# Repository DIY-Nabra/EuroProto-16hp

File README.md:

EURORACK PROTOBOARD 16HP
========================

A universal Eurorack module building system inspired by [Serge Modular Paperface](https://serge-modular.com/paperface),
and Delptronics [Module Construction Set](https://delptronics.com/module-construction-set.php).

All projects in the [DIY-Nabra](https://github.com/DIY-Nabra) repositories are built using this board, or it's little
sibling the [10hp Eurorack Protoboard](https://github.com/DIY-Nabra/EuroProto-10hp)

Licensed under a CC BY-NC-SA 4.0 (Creative Commons Attribution-NonCommercial-ShareAlike 4.0) license.  See the [License File](./LICENSE.md) for more details.

*Front panel*

*Panel components board*

*Front of mainboard*

*Back of mainboard*

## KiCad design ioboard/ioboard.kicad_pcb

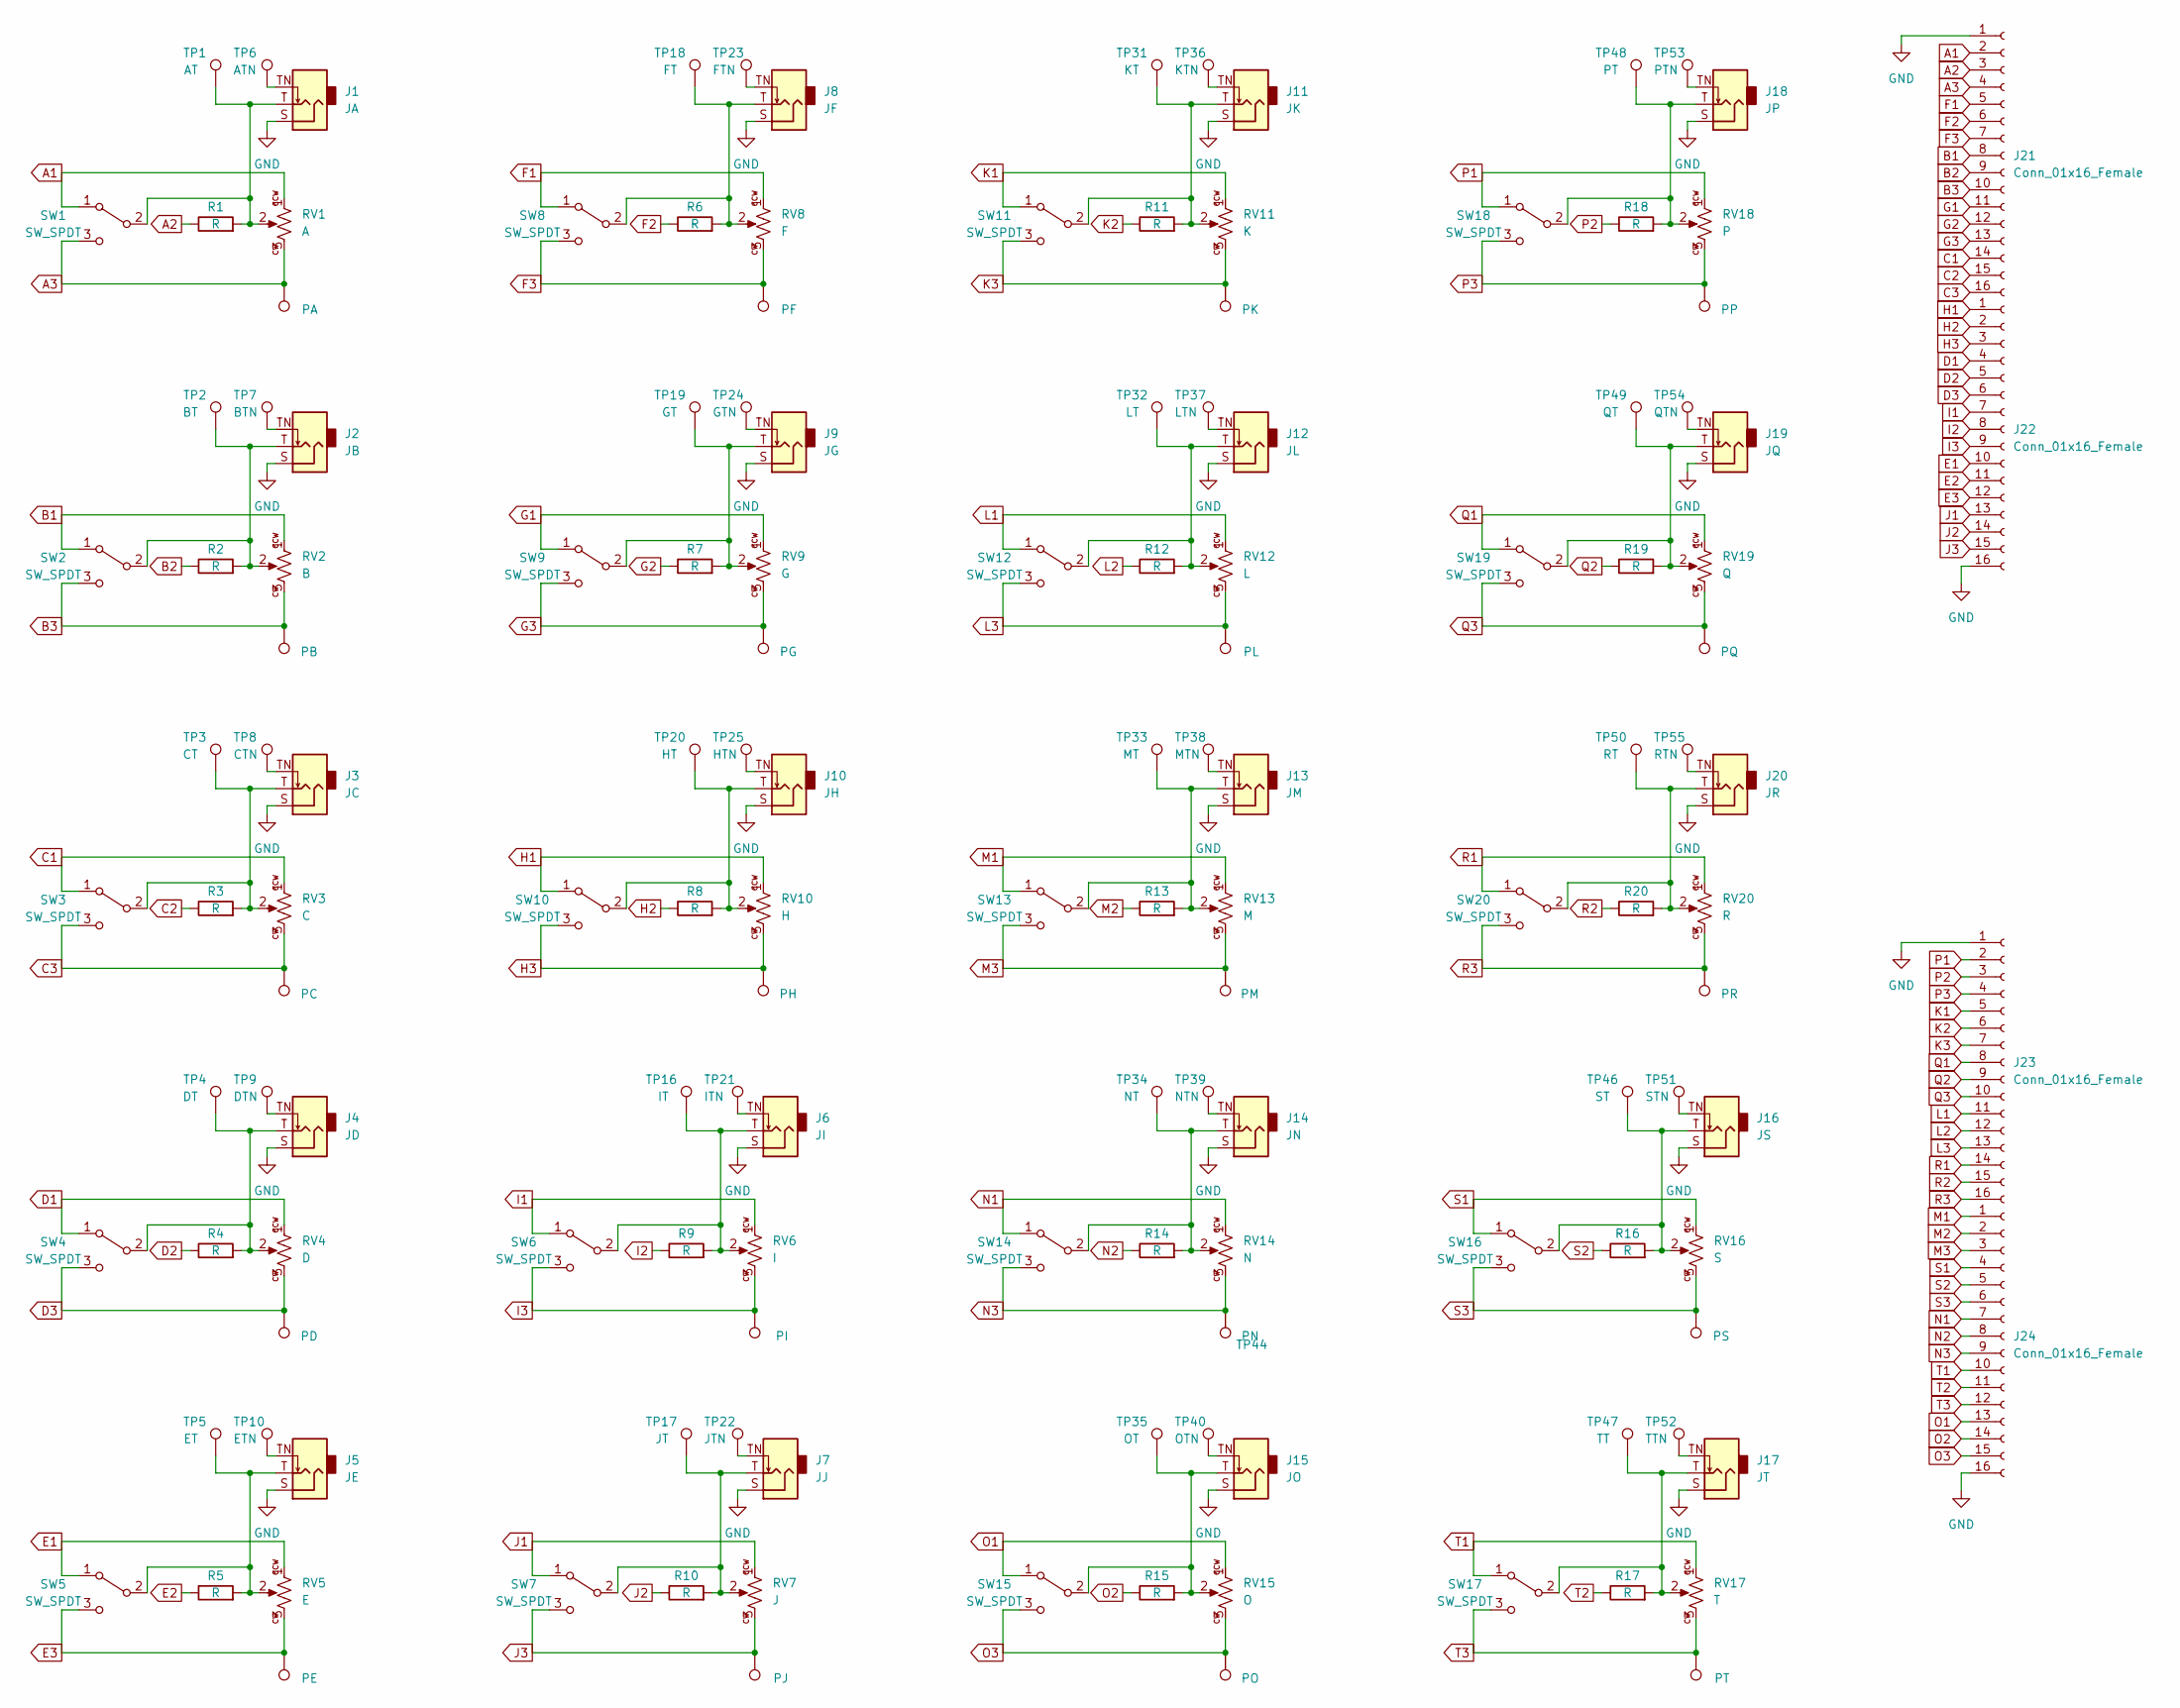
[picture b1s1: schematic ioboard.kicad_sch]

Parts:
J1: JA; slimjackfootprint; MPN WQP-WQP518MA
J2: JB; slimjackfootprint; MPN WQP-WQP518MA
J3: JC; slimjackfootprint; MPN WQP-WQP518MA
J4: JD; slimjackfootprint; MPN WQP-WQP518MA
J5: JE; slimjackfootprint; MPN WQP-WQP518MA
J6: JI; slimjackfootprint; MPN WQP-WQP518MA
J7: JJ; slimjackfootprint; MPN WQP-WQP518MA
J8: JF; slimjackfootprint; MPN WQP-WQP518MA
J9: JG; slimjackfootprint; MPN WQP-WQP518MA
J10: JH; slimjackfootprint; MPN WQP-WQP518MA
J11: JK; slimjackfootprint; MPN WQP-WQP518MA
J12: JL; slimjackfootprint; MPN WQP-WQP518MA
J13: JM; slimjackfootprint; MPN WQP-WQP518MA
J14: JN; slimjackfootprint; MPN WQP-WQP518MA
J15: JO; slimjackfootprint; MPN WQP-WQP518MA
J16: JS; slimjackfootprint; MPN WQP-WQP518MA
J17: JT; slimjackfootprint; MPN WQP-WQP518MA
J18: JP; slimjackfootprint; MPN WQP-WQP518MA
J19: JQ; slimjackfootprint; MPN WQP-WQP518MA
J20: JR; slimjackfootprint; MPN WQP-WQP518MA
J21, J22, J23, J24: Conn_01x16_Female; PinHeader_1x16_P2.54mm_Vertical
R1, R2, R3, R4, R5, R6, R7, R8, R9, R10, R11, R12, R13, R14, R15, R16, R17, R18, R19, R20: R; R_Axial_DIN0204_L3.6mm_D1.6mm_P7.62mm_Horizontal
RV1: A; Potentiometer_Alpha_R0904N; MPN R0904N-???? L-25KQ/LWS
RV2: B; Potentiometer_Alpha_R0904N; MPN R0904N-???? L-25KQ/LWS
RV3: C; Potentiometer_Alpha_R0904N; MPN R0904N-???? L-25KQ/LWS
RV4: D; Potentiometer_Alpha_R0904N; MPN R0904N-???? L-25KQ/LWS
RV5: E; Potentiometer_Alpha_R0904N; MPN R0904N-???? L-25KQ/LWS
RV6: I; Potentiometer_Alpha_R0904N; MPN R0904N-???? L-25KQ/LWS
RV7: J; Potentiometer_Alpha_R0904N; MPN R0904N-???? L-25KQ/LWS
RV8: F; Potentiometer_Alpha_R0904N; MPN R0904N-???? L-25KQ/LWS
RV9: G; Potentiometer_Alpha_R0904N; MPN R0904N-???? L-25KQ/LWS
RV10: H; Potentiometer_Alpha_R0904N; MPN R0904N-???? L-25KQ/LWS
RV11: K; Potentiometer_Alpha_R0904N; MPN R0904N-???? L-25KQ/LWS
RV12: L; Potentiometer_Alpha_R0904N; MPN R0904N-???? L-25KQ/LWS
RV13: M; Potentiometer_Alpha_R0904N; MPN R0904N-???? L-25KQ/LWS
RV14: N; Potentiometer_Alpha_R0904N; MPN R0904N-???? L-25KQ/LWS
RV15: O; Potentiometer_Alpha_R0904N; MPN R0904N-???? L-25KQ/LWS
RV16: S; Potentiometer_Alpha_R0904N; MPN R0904N-???? L-25KQ/LWS
RV17: T; Potentiometer_Alpha_R0904N; MPN R0904N-???? L-25KQ/LWS
RV18: P; Potentiometer_Alpha_R0904N; MPN R0904N-???? L-25KQ/LWS
RV19: Q; Potentiometer_Alpha_R0904N; MPN R0904N-???? L-25KQ/LWS
RV20: R; Potentiometer_Alpha_R0904N; MPN R0904N-???? L-25KQ/LWS
SW1, SW2, SW3, SW4, SW5, SW6, SW7, SW8, SW9, SW10, SW11, SW12, SW13, SW14, SW15, SW16, SW17, SW18, SW19, SW20: SW_SPDT; Miniature_Switch_SPDT_2.54MM
TP1: AT; TestPoint_THTPad_D2.0mm_Drill1.0mm
TP2: BT; TestPoint_THTPad_D2.0mm_Drill1.0mm
TP3: CT; TestPoint_THTPad_D2.0mm_Drill1.0mm
TP4: DT; TestPoint_THTPad_D2.0mm_Drill1.0mm
TP5: ET; TestPoint_THTPad_D2.0mm_Drill1.0mm
TP6: ATN; TestPoint_THTPad_D2.0mm_Drill1.0mm
TP7: BTN; TestPoint_THTPad_D2.0mm_Drill1.0mm
TP8: CTN; TestPoint_THTPad_D2.0mm_Drill1.0mm
TP9: DTN; TestPoint_THTPad_D2.0mm_Drill1.0mm
TP10: ETN; TestPoint_THTPad_D2.0mm_Drill1.0mm
TP11: PA; TestPoint_THTPad_D2.0mm_Drill1.0mm
TP12: PB; TestPoint_THTPad_D2.0mm_Drill1.0mm
TP13: PC; TestPoint_THTPad_D2.0mm_Drill1.0mm
TP14: PD; TestPoint_THTPad_D2.0mm_Drill1.0mm
TP15: PE; TestPoint_THTPad_D2.0mm_Drill1.0mm
TP16: IT; TestPoint_THTPad_D2.0mm_Drill1.0mm
TP17: JT; TestPoint_THTPad_D2.0mm_Drill1.0mm
TP18: FT; TestPoint_THTPad_D2.0mm_Drill1.0mm
TP19: GT; TestPoint_THTPad_D2.0mm_Drill1.0mm
TP20: HT; TestPoint_THTPad_D2.0mm_Drill1.0mm
TP21: ITN; TestPoint_THTPad_D2.0mm_Drill1.0mm
TP22: JTN; TestPoint_THTPad_D2.0mm_Drill1.0mm
TP23: FTN; TestPoint_THTPad_D2.0mm_Drill1.0mm
TP24: GTN; TestPoint_THTPad_D2.0mm_Drill1.0mm
TP25: HTN; TestPoint_THTPad_D2.0mm_Drill1.0mm
TP26: PI; TestPoint_THTPad_D2.0mm_Drill1.0mm
TP27: PJ; TestPoint_THTPad_D2.0mm_Drill1.0mm
TP28: PF; TestPoint_THTPad_D2.0mm_Drill1.0mm
TP29: PG; TestPoint_THTPad_D2.0mm_Drill1.0mm
TP30: PH; TestPoint_THTPad_D2.0mm_Drill1.0mm
TP31: KT; TestPoint_THTPad_D2.0mm_Drill1.0mm
TP32: LT; TestPoint_THTPad_D2.0mm_Drill1.0mm
TP33: MT; TestPoint_THTPad_D2.0mm_Drill1.0mm
TP34: NT; TestPoint_THTPad_D2.0mm_Drill1.0mm
TP35: OT; TestPoint_THTPad_D2.0mm_Drill1.0mm
TP36: KTN; TestPoint_THTPad_D2.0mm_Drill1.0mm
TP37: LTN; TestPoint_THTPad_D2.0mm_Drill1.0mm
TP38: MTN; TestPoint_THTPad_D2.0mm_Drill1.0mm
TP39: NTN; TestPoint_THTPad_D2.0mm_Drill1.0mm
TP40: OTN; TestPoint_THTPad_D2.0mm_Drill1.0mm
TP41: PK; TestPoint_THTPad_D2.0mm_Drill1.0mm
TP42: PL; TestPoint_THTPad_D2.0mm_Drill1.0mm
TP43: PM; TestPoint_THTPad_D2.0mm_Drill1.0mm
TP44: PN; TestPoint_THTPad_D2.0mm_Drill1.0mm
TP45: PO; TestPoint_THTPad_D2.0mm_Drill1.0mm
TP46: ST; TestPoint_THTPad_D2.0mm_Drill1.0mm
TP47: TT; TestPoint_THTPad_D2.0mm_Drill1.0mm
TP48, TP57: PT; TestPoint_THTPad_D2.0mm_Drill1.0mm
TP49: QT; TestPoint_THTPad_D2.0mm_Drill1.0mm
TP50: RT; TestPoint_THTPad_D2.0mm_Drill1.0mm
TP51: STN; TestPoint_THTPad_D2.0mm_Drill1.0mm
TP52: TTN; TestPoint_THTPad_D2.0mm_Drill1.0mm
TP53: PTN; TestPoint_THTPad_D2.0mm_Drill1.0mm
TP54: QTN; TestPoint_THTPad_D2.0mm_Drill1.0mm
TP55: RTN; TestPoint_THTPad_D2.0mm_Drill1.0mm
TP56: PS; TestPoint_THTPad_D2.0mm_Drill1.0mm
TP58: PP; TestPoint_THTPad_D2.0mm_Drill1.0mm
TP59: PQ; TestPoint_THTPad_D2.0mm_Drill1.0mm
TP60: PR; TestPoint_THTPad_D2.0mm_Drill1.0mm

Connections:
A1: J21.2, RV1.1, SW1.1 (A)
A2: J21.3, R1.1
A3: J21.4, RV1.3, SW1.3 (C), TP11.1
B1: J21.8, RV2.1, SW2.1 (A)
B2: J21.9, R2.1
B3: J21.10, RV2.3, SW2.3 (C), TP12.1
C1: J21.14, RV3.1, SW3.1 (A)
C2: J21.15, R3.1
C3: J21.16, RV3.3, SW3.3 (C), TP13.1
D1: J22.4, RV4.1, SW4.1 (A)
D2: J22.5, R4.1
D3: J22.6, RV4.3, SW4.3 (C), TP14.1
E1: J22.10, RV5.1, SW5.1 (A)
E2: J22.11, R5.1
E3: J22.12, RV5.3, SW5.3 (C), TP15.1
F1: J21.5, RV8.1, SW8.1 (A)
F2: J21.6, R6.1
F3: J21.7, RV8.3, SW8.3 (C), TP28.1
G1: J21.11, RV9.1, SW9.1 (A)
G2: J21.12, R7.1
G3: J21.13, RV9.3, SW9.3 (C), TP29.1
GND: J1.S (Sleeve), J2.S (Sleeve), J3.S (Sleeve), J4.S (Sleeve), J5.S (Sleeve), J6.S (Sleeve), J7.S (Sleeve), J8.S (Sleeve), J9.S (Sleeve), J10.S (Sleeve), J11.S (Sleeve), J12.S (Sleeve), J13.S (Sleeve), J14.S (Sleeve), J15.S (Sleeve), J16.S (Sleeve), J17.S (Sleeve), J18.S (Sleeve), J19.S (Sleeve), J20.S (Sleeve), J21.1, J22.16, J23.1, J24.16
H1: J22.1, RV10.1, SW10.1 (A)
H2: J22.2, R8.1
H3: J22.3, RV10.3, SW10.3 (C), TP30.1
I1: J22.7, RV6.1, SW6.1 (A)
I2: J22.8, R9.1
I3: J22.9, RV6.3, SW6.3 (C), TP26.1
J1: J22.13, RV7.1, SW7.1 (A)
J2: J22.14, R10.1
J3: J22.15, RV7.3, SW7.3 (C), TP27.1
K1: J23.5, RV11.1, SW11.1 (A)
K2: J23.6, R11.1
K3: J23.7, RV11.3, SW11.3 (C), TP41.1
L1: J23.11, RV12.1, SW12.1 (A)
L2: J23.12, R12.1
L3: J23.13, RV12.3, SW12.3 (C), TP42.1
M1: J24.1, RV13.1, SW13.1 (A)
M2: J24.2, R13.1
M3: J24.3, RV13.3, SW13.3 (C), TP43.1
N1: J24.7, RV14.1, SW14.1 (A)
N2: J24.8, R14.1
N3: J24.9, RV14.3, SW14.3 (C), TP44.1
unnamed: J1.T (Tip), R1.2, RV1.2, SW1.2 (B), TP1.1
unnamed: J1.TN (Tip_normalize), TP6.1
unnamed: J2.T (Tip), R2.2, RV2.2, SW2.2 (B), TP2.1
unnamed: J2.TN (Tip_normalize), TP7.1
unnamed: J3.T (Tip), R3.2, RV3.2, SW3.2 (B), TP3.1
unnamed: J3.TN (Tip_normalize), TP8.1
unnamed: J4.T (Tip), R4.2, RV4.2, SW4.2 (B), TP4.1
unnamed: J4.TN (Tip_normalize), TP9.1
unnamed: J5.T (Tip), R5.2, RV5.2, SW5.2 (B), TP5.1
unnamed: J5.TN (Tip_normalize), TP10.1
unnamed: J6.T (Tip), R9.2, RV6.2, SW6.2 (B), TP16.1
unnamed: J6.TN (Tip_normalize), TP21.1
unnamed: J7.T (Tip), R10.2, RV7.2, SW7.2 (B), TP17.1
unnamed: J7.TN (Tip_normalize), TP22.1
unnamed: J8.T (Tip), R6.2, RV8.2, SW8.2 (B), TP18.1
unnamed: J8.TN (Tip_normalize), TP23.1
unnamed: J9.T (Tip), R7.2, RV9.2, SW9.2 (B), TP19.1
unnamed: J9.TN (Tip_normalize), TP24.1
unnamed: J10.T (Tip), R8.2, RV10.2, SW10.2 (B), TP20.1
unnamed: J10.TN (Tip_normalize), TP25.1
unnamed: J11.T (Tip), R11.2, RV11.2, SW11.2 (B), TP31.1
unnamed: J11.TN (Tip_normalize), TP36.1
unnamed: J12.T (Tip), R12.2, RV12.2, SW12.2 (B), TP32.1
unnamed: J12.TN (Tip_normalize), TP37.1
unnamed: J13.T (Tip), R13.2, RV13.2, SW13.2 (B), TP33.1
unnamed: J13.TN (Tip_normalize), TP38.1
unnamed: J14.T (Tip), R14.2, RV14.2, SW14.2 (B), TP34.1
unnamed: J14.TN (Tip_normalize), TP39.1
unnamed: J15.T (Tip), R15.2, RV15.2, SW15.2 (B), TP35.1
unnamed: J15.TN (Tip_normalize), TP40.1
unnamed: J16.T (Tip), R16.2, RV16.2, SW16.2 (B), TP46.1
unnamed: J16.TN (Tip_normalize), TP51.1
unnamed: J17.T (Tip), R17.2, RV17.2, SW17.2 (B), TP47.1
unnamed: J17.TN (Tip_normalize), TP52.1
unnamed: J18.T (Tip), R18.2, RV18.2, SW18.2 (B), TP48.1
unnamed: J18.TN (Tip_normalize), TP53.1
unnamed: J19.T (Tip), R19.2, RV19.2, SW19.2 (B), TP49.1
unnamed: J19.TN (Tip_normalize), TP54.1
unnamed: J20.T (Tip), R20.2, RV20.2, SW20.2 (B), TP50.1
unnamed: J20.TN (Tip_normalize), TP55.1
O1: J24.13, RV15.1, SW15.1 (A)
O2: J24.14, R15.1
O3: J24.15, RV15.3, SW15.3 (C), TP45.1
P1: J23.2, RV18.1, SW18.1 (A)
P2: J23.3, R18.1
P3: J23.4, RV18.3, SW18.3 (C), TP58.1
Q1: J23.8, RV19.1, SW19.1 (A)
Q2: J23.9, R19.1
Q3: J23.10, RV19.3, SW19.3 (C), TP59.1
R1: J23.14, RV20.1, SW20.1 (A)
R2: J23.15, R20.1
R3: J23.16, RV20.3, SW20.3 (C), TP60.1
S1: J24.4, RV16.1, SW16.1 (A)
S2: J24.5, R16.1
S3: J24.6, RV16.3, SW16.3 (C), TP56.1
T1: J24.10, RV17.1, SW17.1 (A)
T2: J24.11, R17.1
T3: J24.12, RV17.3, SW17.3 (C), TP57.1

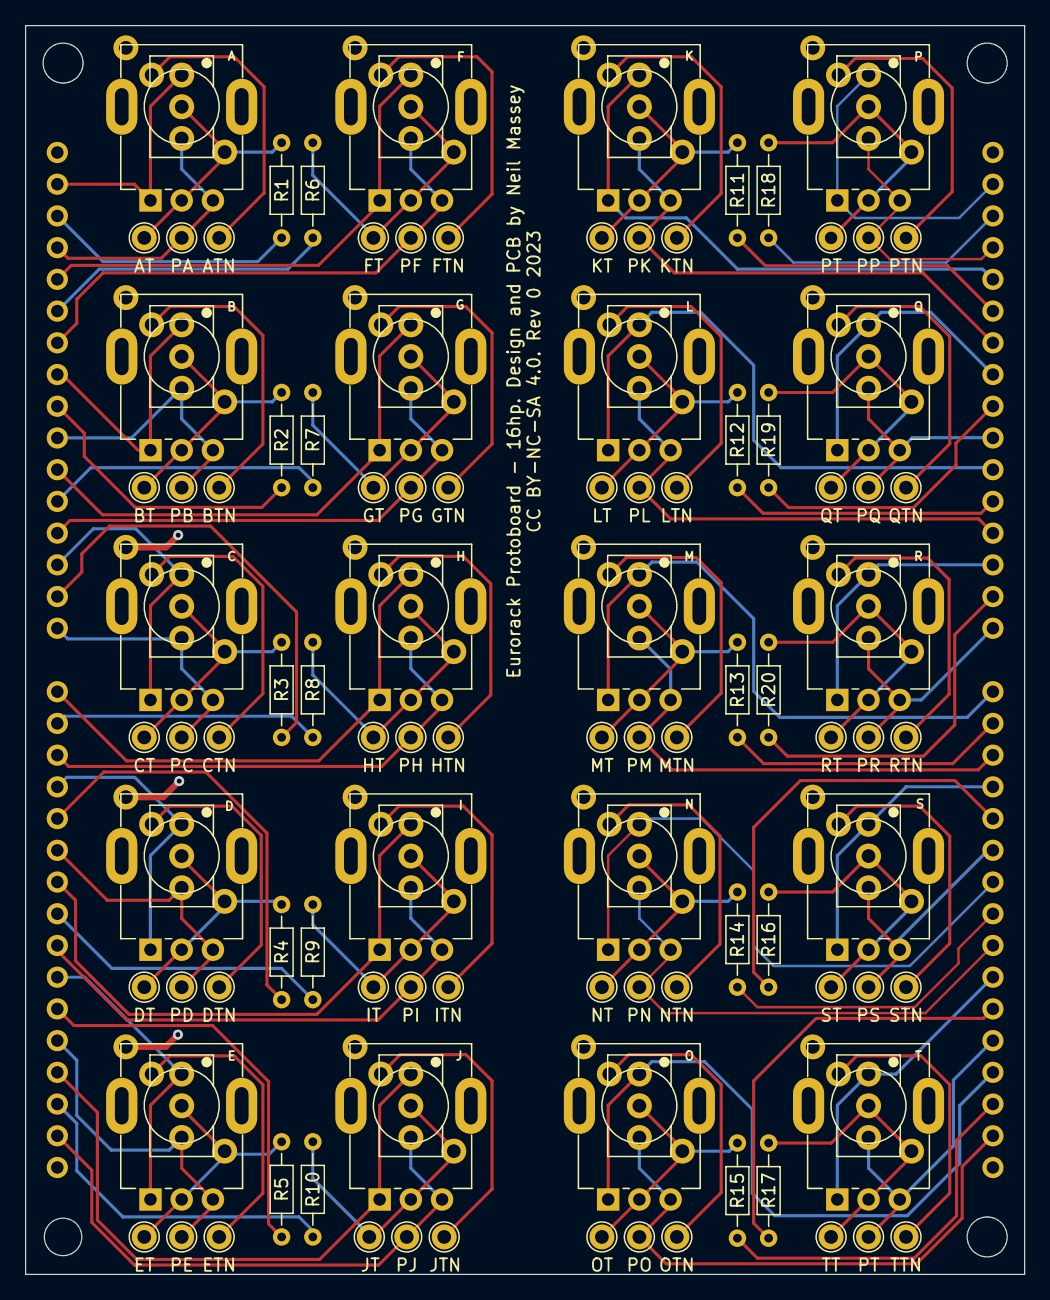
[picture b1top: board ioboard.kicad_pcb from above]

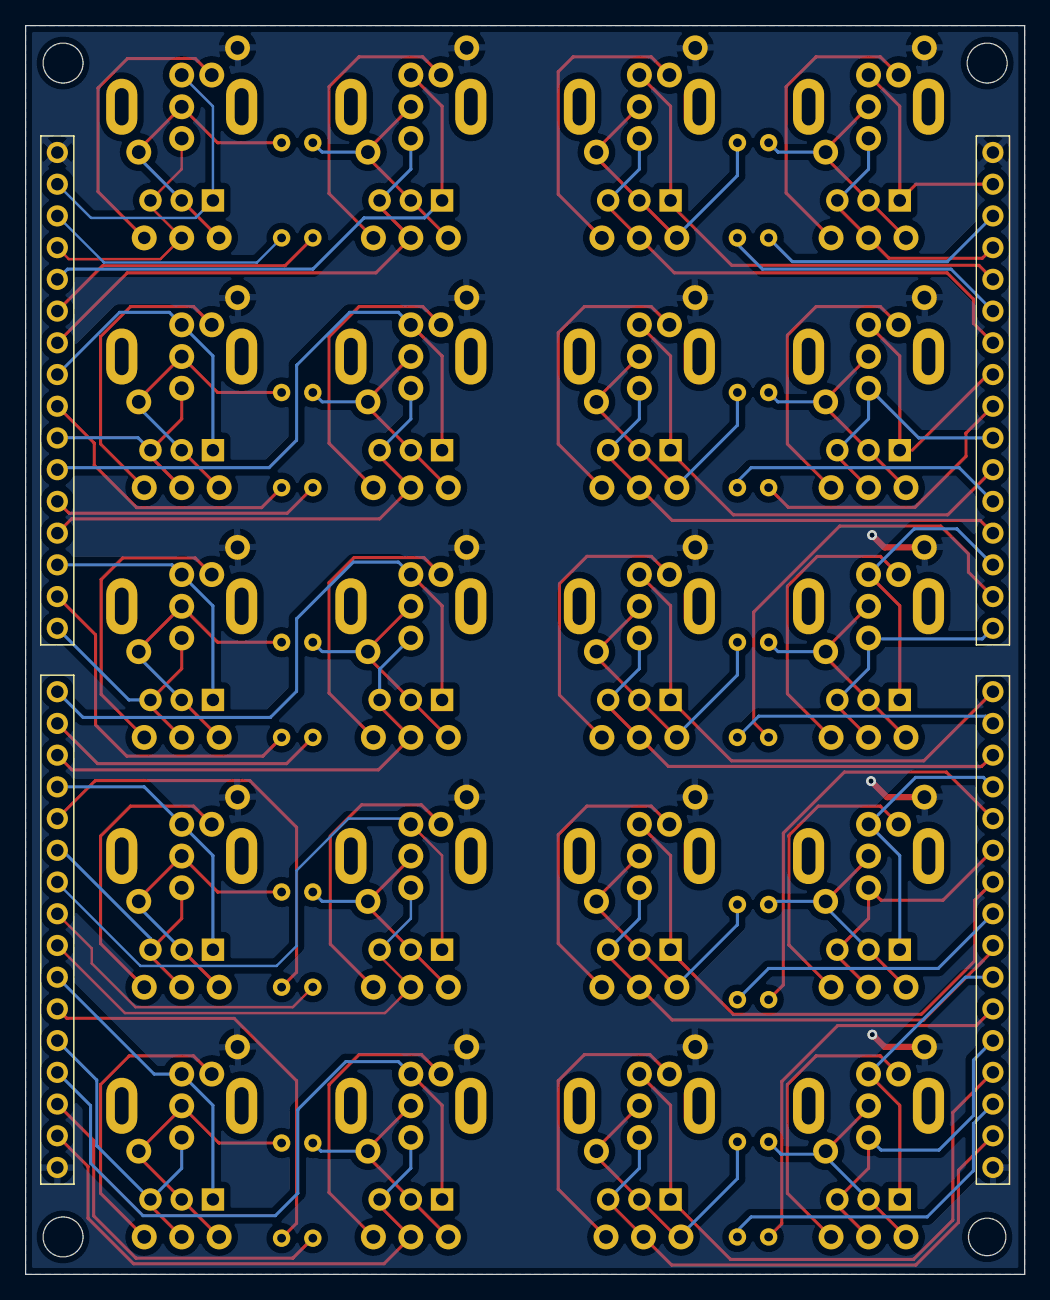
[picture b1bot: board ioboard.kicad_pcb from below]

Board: 2 copper layers, 80.0 x 100.0 mm, 144 parts (4 on the bottom side), 101 nets.

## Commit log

2023-05-19 Resized assets
2024-09-21 Added template

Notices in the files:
ioboard/ioboard.kicad_pcb:
CC BY-NC-SA 4.0. Rev 0 2023
